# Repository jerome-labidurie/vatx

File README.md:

Simple breakoutboard to use an ATX PSU as variable PSU
======================================================

* Goal is to use a un-modified ATX PSU.
* mostly one side-PCB for very simple creation
* Use banana plugs for every voltage
* Use LM317 for 1.5A variable voltage (~ 3-11V)
* USB connector for particular devices
* StandBy/Power leds
* OpenHardware CC:BY-SA http://creativecommons.org/licenses/by-sa/3.0/

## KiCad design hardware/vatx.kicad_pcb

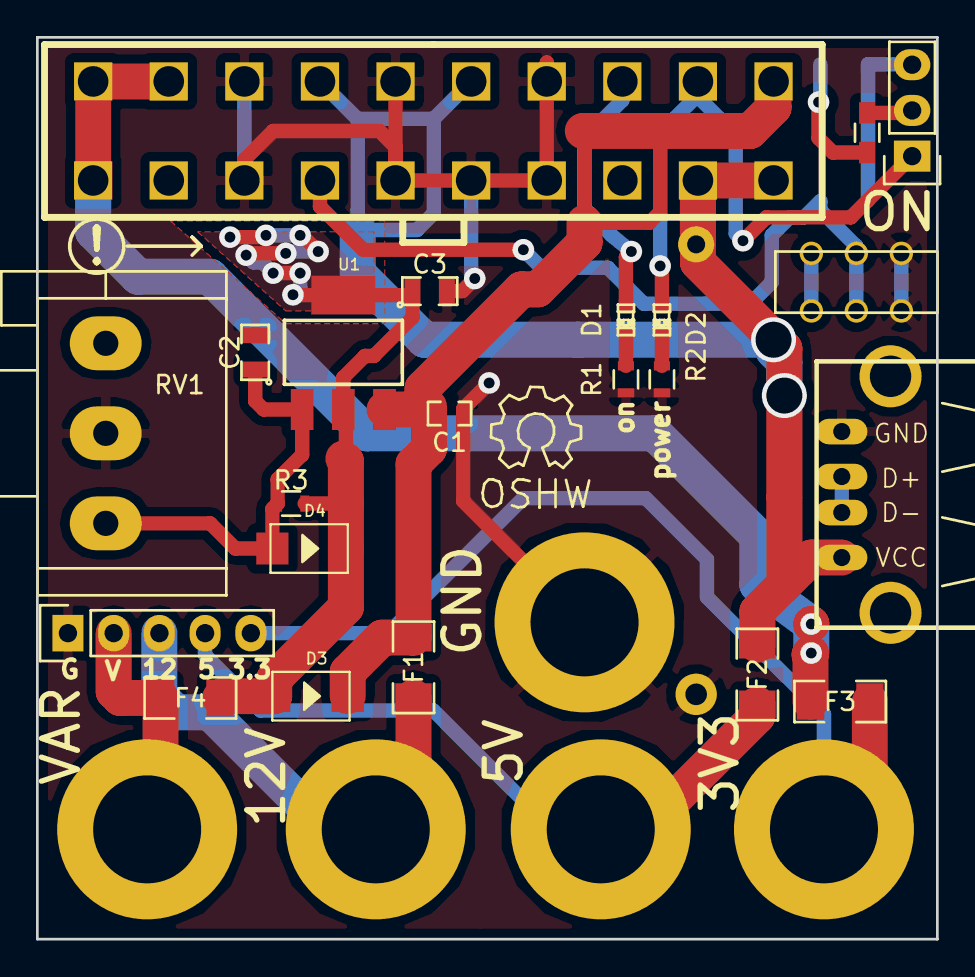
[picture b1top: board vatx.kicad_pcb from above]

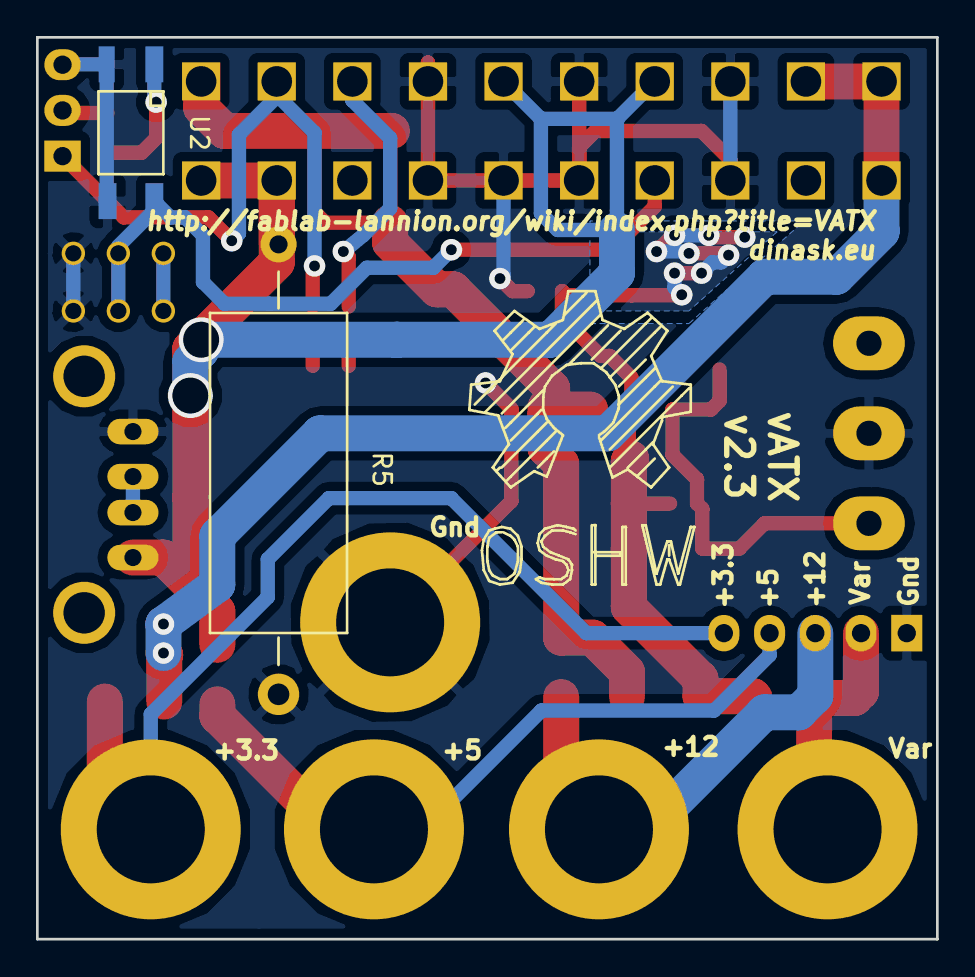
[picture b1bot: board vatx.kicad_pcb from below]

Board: 2 copper layers, 50.0 x 50.1 mm, 31 parts (3 on the bottom side), 18 nets.

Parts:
C1: 0.1µF; SMD-0603_c
C2: 10µF; SMD-0805
C3: 1µF; SMD-0805
D1: blue; LED-0603
D2: yellow; LED-0603
D3, D4: 1N4007; DO-214AC
F1, F2, F3, F4: FUSE; SMD-1206
J1: USB; 4P-2.0-90D
P1: CONN_10X2; ATX_NON_90DEG
P2: CONN_01X05; Pin_Header_Straight_1x05
P3, P4, P5, P6, P7: CONN_1; Banana_single_6mmDrill
P8: CONN_01X03; Pin_Header_Straight_1x03
R1: 470; R_0603
R2: 680; R_0603
R3: 100; R_0603
R4: R; R_0603_HandSoldering
R5: 10 9W; Resistor_Horizontal_RM25mm
RV1: 1K; Potentiometer_Alps-RK16-single_largePads
SW1: SWITCH_INV; TS-1101F
Symbol_OSHW-Logo_SilkScreen: VAL**; Symbol_OSHW-Logo_SilkScreen
Symbol_OSHW-Logo_SilkScreen_BIG: VAL**; Symbol_OSHW-Logo_SilkScreen_BIG
U1: LM317T; SOT223
U2: OPTO-TRANSISTOR4; Optocoupler_SMD_HandSoldering_KPC357_LTV35x_PC357_SingleCha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

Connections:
+3.3V: F3.1, P1.1, P1.2, P1.3
+5V: F2.1, J1.1, P1.7, P1.11, P1.18, P1.20, R5.1
+5VSB: D2.1, P1.17, P8.1
+12V: C1.1, D3.2, F1.1, P1.19, U1.3
+VAR: C3.1, D3.1, D4.2, F4.1, R3.1, U1.2
GND: C1.2, C2.2, C3.2, J1.4, P1.5, P1.6, P1.9, P1.10, P1.12, P1.13, P1.14, P2.1, P7.1, P8.3, R1.2, R2.2, R5.2, RV1.2, SW1.3, U2.2, U2.3
unnamed: C2.1, D4.1, R3.2, RV1.1, U1.1
unnamed: D1.2, R1.1
unnamed: D2.2, R2.1
unnamed: J1.2, J1.3
unnamed: P8.2, R4.1
unnamed: R4.2, U2.1
POK: D1.1, P1.15
PSON: P1.8, SW1.2, U2.4
f+3.3V: F3.2, P2.5, P5.1
f+5V: F2.2, P2.4, P4.1
f+12V: F1.2, P2.3, P3.1
f+VAR: F4.2, P2.2, P6.1

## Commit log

2014-04-19 first import
2014-04-19 Add fabrications files/pdf
2014-09-28 Mounting holes
2014-12-19 Move to a smaller board * remove load resistor * remove -5 / -12 * 50x50mm pcb * SMD components for seeedstudio OPL
    TODO:
    * switch footprint
    * check diodes footprint
    * silkscreen
2015-03-09 Short between D+/D- to be an USB DCP http://www.maximintegrated.com/en/app-notes/index.mvp/id/4803
2015-03-09 Silkscreen
2015-03-09 LM317 heatsink
2015-03-10 room for 24pins ATX connector seeed opl switch footprint seeed opl usb A footprint fused +5V for usb leds on/power labels paste for heatsink
2015-03-10 +VAR vias
2015-03-10 scheme/pcb version again via for heatsink
2015-03-10 Add power resistor some PSU need that to deliver current
2015-03-11 Set seeed opl diode footprint
2015-03-11 Update +VAR : remove R4 R1/R2 values updated for choosen leds Seeed BOM
2015-03-11 documentation
2015-03-11 Add pin-header for every voltage
2015-03-24 led doc
2015-03-24 scheme for optional PSON control
2015-03-24 pcb for optional PSON control
2015-03-25 Remove fuse for 5V usb
2015-03-25 Fabrication files for v2.2
2015-03-27 add production tests document
2015-04-30 3D file for box 1st batch pictures
2015-05-06 box bug hole for gnd plug
2015-05-12 Corrected box
2015-05-18 3d model for potentiometer knob
2015-05-18 V2.2 bugfix & enhancement * potentiometer connection * power/on silkscreen * more 0.8 traces for power traces (+12V, +5V) * more via for power traces (+5V, +3.3V)
2015-05-29 Add silk rectangle for serial #
2015-05-29 Simplify 3D box design to speedup printing
2015-05-29 Correction of pot shaft diameter
2015-06-01 Add external control exemple
2015-06-01 Add pictures explaining how to populate external control components
